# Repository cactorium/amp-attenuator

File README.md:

# 8 Ohm fixed level audio attenuator
This is a circuit to attenuate tube amp outputs to get power stage distortion at apartment-preferred levels.
Just stick between the amp and the 8 ohm speaker, and it'll attenuate the power by a fixed amount.
It's currently untested, but the boards should be ordered by the time this is published.
It should be safe to use for up to 10 W tube amps, and probably safe up to 20-25 W.
It's a simple T-pad attenuator, using one or two Yageo SQP10A (or equivalently sized) resistors for each of the three resistances.
Below is the BOM for various attenuation levels:

|Attenuation level|R1|R2|R3|R4|R5|R6|J1|J2|
|----|----|----|---|---|---|---|--|--|
|-3 dB|SQP10A-2R7|SQP10A-2R7|SQP10A-22R|DNP|SQP10A-2R7|SQP10A-2R7|NYS216|NYS216|
|-6 dB|SQP10A-2R7|DNP|SQP10A-22R|SQP10A-22R|SQP10A-2R7|DNP|NYS216|NYS216|
|-10 dB|SQP10A-4R7|DNP|SQP10A-5R6|DNP|SQP10A-4R7|DNP|NYS216|NYS216|
|-12 dB|SQP10A-4R7|DNP|SQP10A-8R2|SQP10A-8R2|SQP10A-4R7|DNP|NYS216|NYS216|

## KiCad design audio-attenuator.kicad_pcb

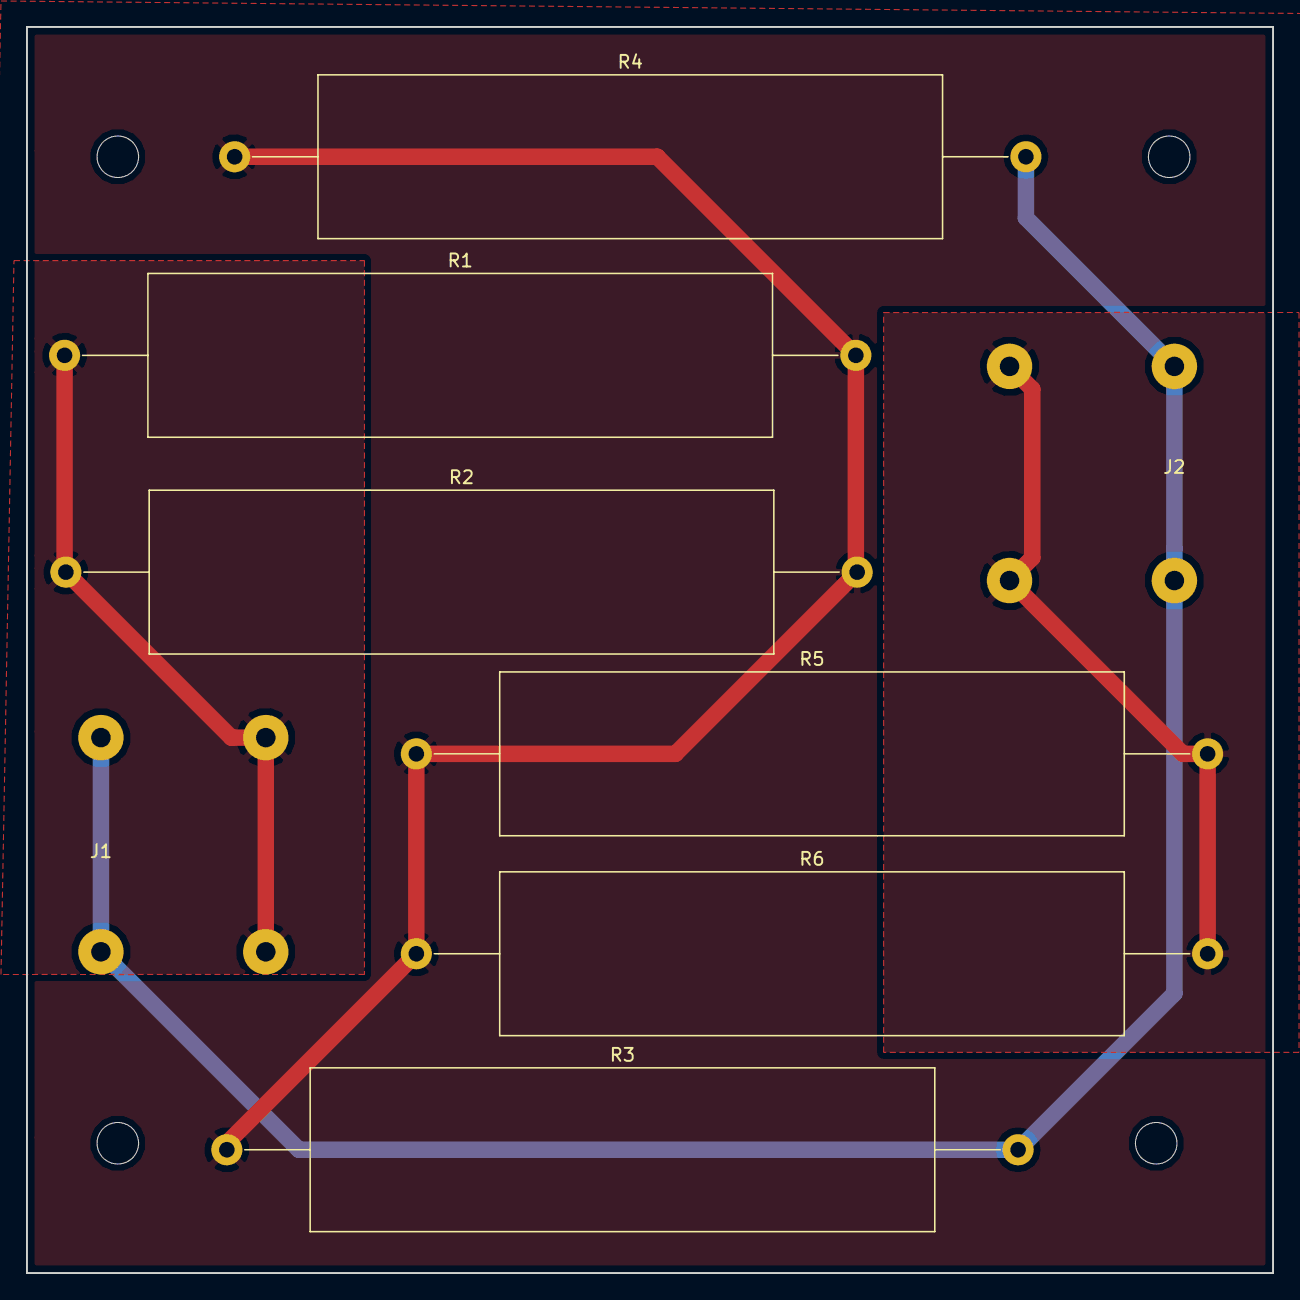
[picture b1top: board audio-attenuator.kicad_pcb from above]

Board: 2 copper layers, 96.0 x 96.0 mm, 12 parts (0 on the bottom side), 4 nets.

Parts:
J1, J2: AudioJack2_Ground; NYS2162-U
MH1, MH2, MH3, MH4: MountingHole; MountingHole_3.2mm_M3
R1, R2, R3, R4, R5, R6: TBD; R_Axial_Power_L48.0mm_W12.5mm_P60.96mm

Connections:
/ATTEN: R1.2, R2.2, R3.1, R4.1, R5.1, R6.1
/IN: J1.T, R1.1, R2.1
/OUT: J2.T, R5.2, R6.2
GND: J1.S, J2.S, R3.2, R4.2

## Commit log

2018-09-30 First revision
2018-09-30 Fix README
2018-09-30 Generate PDF
2018-12-05 Zip Gerbers for sending to fab
